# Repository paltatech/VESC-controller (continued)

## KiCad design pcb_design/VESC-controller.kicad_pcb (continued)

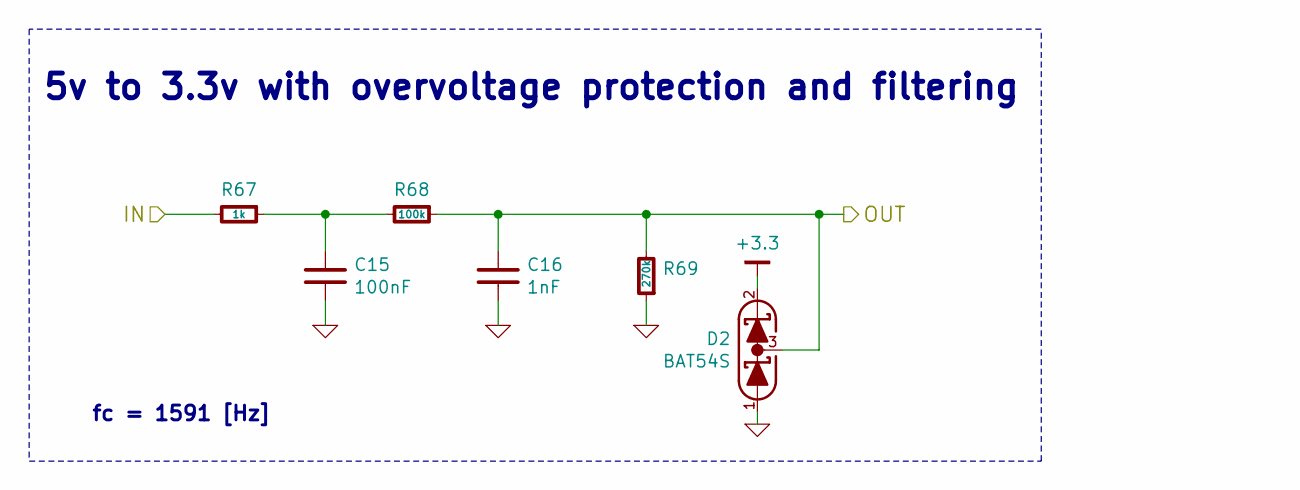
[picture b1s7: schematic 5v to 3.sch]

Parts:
C13: 100nF; CAPC1608X55; MPN GRM188R71E104KA01D
C14: 1nF; CAPC1608X55; MPN GRM188R71H102KA01D
D1: BAT54S; SOT-23; mfg# TBAT54S,LM
R64: 1k; RESC1608X50; MPN RC0603FR-071KL
R65: 100k; RESC1608X50; MPN RC0603FR-07100KL
R66: 270k; RESC1608X50; MPN RC0603FR-07270KL

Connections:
+3.3: D1.2 (K); also elsewhere on the board
/Accel input conditioning/IN: R64.2; also elsewhere on the board
/STM32F4/ADC_15: C14.1, D1.3 (COM), R65.1, R66.2; also elsewhere on the board
unnamed: C13.1, R64.1, R65.2

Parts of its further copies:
C15: 100nF; CAPC1608X55; MPN GRM188R71E104KA01D
C16: 1nF; CAPC1608X55; MPN GRM188R71H102KA01D
D2: BAT54S; SOT-23; mfg# TBAT54S,LM
R67: 1k; RESC1608X50; MPN RC0603FR-071KL
R68: 100k; RESC1608X50; MPN RC0603FR-07100KL
R69: 270k; RESC1608X50; MPN RC0603FR-07270KL

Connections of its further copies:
+3.3: D2.2 (K); also elsewhere on the board
/Regen input conditioning/IN: R67.2; also elsewhere on the board
/STM32F4/ADC_8: C16.1, D2.3 (COM), R68.1, R69.2; also elsewhere on the board
unnamed: C15.1, R67.1, R68.2

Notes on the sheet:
5v to 3.3v with overvoltage protection and filtering
fc = 1591 [Hz]

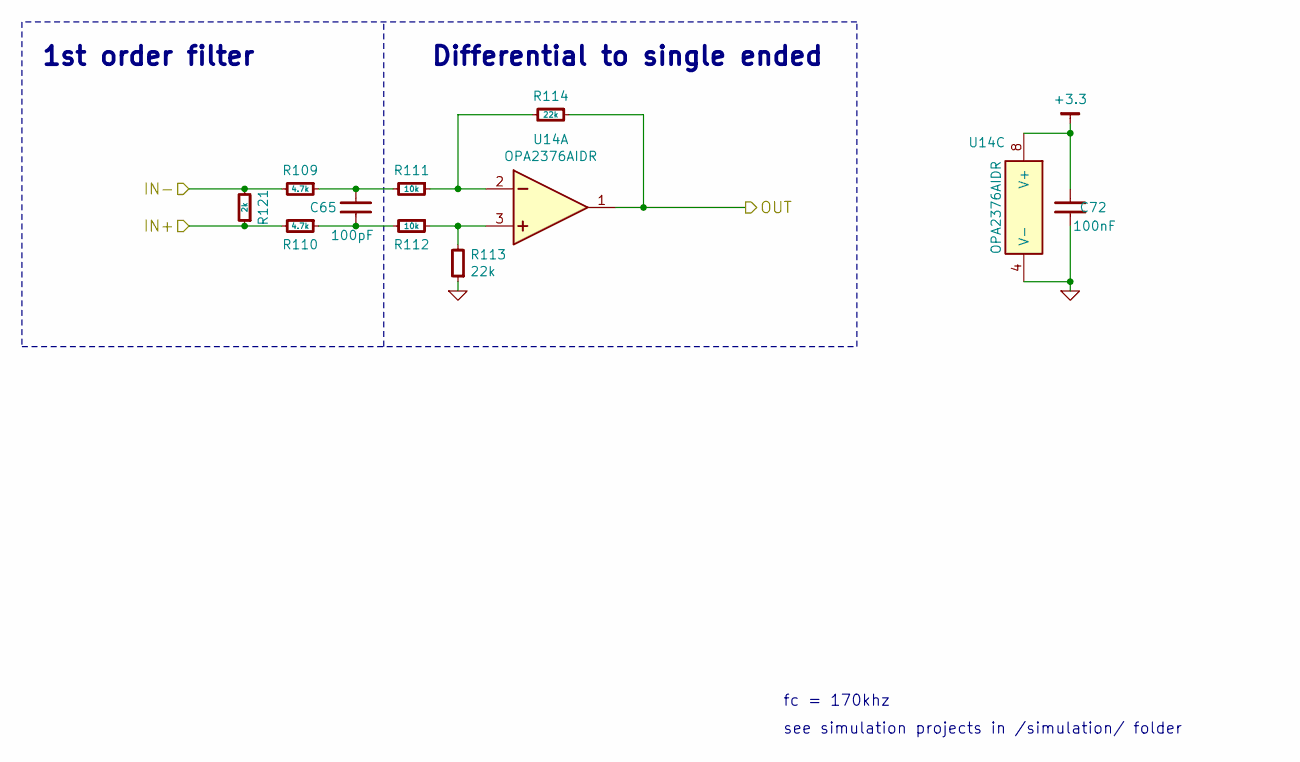
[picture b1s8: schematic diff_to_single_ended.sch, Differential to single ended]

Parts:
C65: 100pF; CAPC1608X55; MPN C0603C101J5GACTU
C72: 100nF; CAPC1608X55; MPN GRM188R71E104KA01D
R109, R110: 4.7k; RESC1608X50; MPN RC0603FR-074K7L
R111, R112: 10k; RESC1608X50; MPN RC0603FR-0710KL
R113, R114: 22k; RESC1608X50; MPN RC0603FR-0722KL
R121: 2k; RESC1608X50; MPN RC0603FR-072KL
U14: OPA2376AIDR; SOIC127P600X175-8; MPN OPA2376AIDR

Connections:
+3.3: C72.1, U14.8 (V+); also elsewhere on the board
/V_bus+: R110.2, R121.1; also elsewhere on the board
/V_bus-: R109.2, R121.2; also elsewhere on the board
/Vbus_conditioning/OUT: R114.1, U14.1 (OUT); also elsewhere on the board
unnamed: C65.1, R109.1, R111.2
unnamed: C65.2, R110.1, R112.2
unnamed: R111.1, R114.2, U14.2 (IN-)
unnamed: R112.1, R113.2, U14.3 (IN+)

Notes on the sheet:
Differential to single ended
1st order filter
fc = 170khz
see simulation projects in /simulation/ folder

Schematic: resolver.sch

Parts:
C73, C74, C75, C77, C81, C82, C85, C86, C87: 100nF; CAPC1608X55; MPN GRM188R71E104KA01D
C76, C78: 2.2uF; CAPC1608X55; MPN GRM188R71A225KE15D
C79, C80: 15pF; CAPC1608X55; MPN GCM1885C1H150JA16D
C83, C84: 120pF; CAPC1608X55; MPN C0603C121F5GACTU
C88, C89: 22uF; CAPC2012X70; mfg# C2012X5R1V226M125AC
E5, E6: BEAD-220ohm@100khz; INDC2012X130; mfg# BLM21PG221SN1D
R124, R125: 68.1k; RESC1608X50; MPN RC0603FR-0768K1L
R126, R128, R130, R131: 10k; RESC1608X50; MPN RC0603FR-0710KL
R127, R129: 22k; RESC1608X50; MPN RC0603FR-0722KL
R132, R133: 15.4k; RESC1608X50; MPN RC0603FR-0715K4L
R136, R137: 0R; RESC1608X50; MPN RC0603JR-070RL
U15: AD2S1205; QFP80P1200X1200X160-44; mfg# AD2S1205
U18: SN74LVC1G; SC-70-6; mfg# SN74LVC1G11IDCKRQ1
U19: AD8397; SOIC127P600X175-8; mfg# AD8397ARZ
U20: APX809; SOT-23; mfg# APX809-46SRG-7
U21: NCV78Mxx; TO-252; mfg# NCV78M12BDTRKG
X1: ABM3B - 8MHz; OSCCC320X500X150; mfg# ABM3B-8.000MHZ-10-1UT

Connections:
+3.3: C75.1, U18.5 (VCC); also elsewhere on the board
+12: C85.1, C88.1, C89.1, E6.2, R127.2, R129.2, U19.8 (V+)
/STM32F4/PB3: U15.4 (~SAMPLE); also elsewhere on the board
/STM32F4/PC12: U15.5 (~RDVEL); also elsewhere on the board
/STM32F4/PD2: U18.4 (QA); also elsewhere on the board
/STM32F4/SPI3_NSS: U15.2 (RD), U15.3 (~CS); also elsewhere on the board
/resolver/CLK: U15.8 (DB10/SCLK); also elsewhere on the board
/resolver/COS+: R125.1, U15.41 (Cos); also elsewhere on the board
/resolver/COS-: R125.2, U15.40 (CosLO); also elsewhere on the board
/resolver/EXC+: C83.1, R132.1, U19.7 (OUT); also elsewhere on the board
/resolver/EXC-: C84.1, R133.1, U19.1 (OUT); also elsewhere on the board
/resolver/EXC_SOURCE+: R126.2, U15.34 (EXC)
/resolver/EXC_SOURCE-: R128.2, U15.35 (~EXC)
/resolver/MISO: U15.7 (DB11/SO); also elsewhere on the board
/resolver/SIN+: R124.1, U15.37 (Sin); also elsewhere on the board
/resolver/SIN-: R124.2, U15.38 (SinLO); also elsewhere on the board
unnamed: C77.1, C78.1, E5.1, U15.39 (AVDD)
unnamed: C79.1, U15.22 (CLKIN), X1.1
unnamed: C80.1, U15.21 (XTALOUT), X1.3
unnamed: C81.1, R129.1, R131.2, U19.3 (IN+)
unnamed: C82.1, R127.1, R130.2, U19.5 (IN+)
unnamed: C83.2, R126.1, R132.2, U19.6 (IN-)
unnamed: C84.2, R128.1, R133.2, U19.2 (IN-)
unnamed: C87.1, E6.1, U21.2 (OUT)
unnamed: R136.2, U15.31 (FS1)
unnamed: R137.2, U15.32 (FS2)
unnamed: U15.6 (~SOE), U18.1 (D1A)
unnamed: U15.29 (~DOS), U18.3 (D2A)
unnamed: U15.30 (~LOT), U18.6 (D3A)
unnamed: U15.33 (~RESET), U20.2

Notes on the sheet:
Resolver interface
Buffer
This is an alternative buffer suggested here: http://www.analog.com/en/analog-dialogue/articles/precision-rtdc-measures-angular-position-and-velocity.html It seems to invert the signal... Its more expensive, but much simpler and smaller
RESET line requires a voltage monitor

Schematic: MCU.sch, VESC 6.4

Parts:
C10, C11, C12, C30, C32, C34: 100nF; CAPC1608X55; MPN GRM188R71E104KA01D
C17, C33: 15pF; CAPC1608X55; MPN GCM1885C1H150JA16D
C28, C29, C31: 2.2uF; CAPC1608X55; MPN GRM188R71A225KE15D
E4: BEAD-220ohm@100khz; INDC2012X130; MPN BLM21PG221SN1D
J9: SWD; CONN-100MIL-M-1x5
R122: 1k; RESC1608X50; MPN RC0603FR-071KL
SW1: BOOTLOADER; SMD-Switch_B3U-1000-B; mfg# B3U-1000P
U1: STM32F40X_LQFP64; QFP50P1200X1200X100-64; MPN STM32F405RGT6
X2: ABM3B - 8MHz; OSCCC320X500X150; mfg# ABM3B-8.000MHZ-10-1UT

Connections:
+3.3: C10.1, C11.1, C12.1, C34.1, E4.2, J9.1, SW1.2, U1.1 (VBAT), U1.19 (VDD), U1.32 (VDD), U1.48 (VDD), U1.64 (VDD); also elsewhere on the board
+3.3A: C30.1, C31.1, E4.1, U1.13 (VDDA); also elsewhere on the board
/Filters/HALL1_OUT: U1.37 (PC6); also elsewhere on the board
/Filters/HALL2_OUT: U1.38 (PC7); also elsewhere on the board
/Filters/HALL3_OUT: U1.39 (PC8); also elsewhere on the board
/Filters/TEMP_IN: U1.24 (PC4(ADC12_IN14)); also elsewhere on the board
/Isolated CAN/CAN_RX: U1.61 (PB8); also elsewhere on the board
/Isolated CAN/CAN_TX: U1.62 (PB9); also elsewhere on the board
/Protected GPIOs/IN1: U1.58 (PB6); also elsewhere on the board
/Protected GPIOs/IN2: U1.23 (PA7(ADC12_IN7)); also elsewhere on the board
/STM32F4/ADC_8: U1.26 (PB0(ADC12_IN8)); also elsewhere on the board
/STM32F4/ADC_15: U1.25 (PC5(ADC12_IN15)); also elsewhere on the board
/STM32F4/ADC_TEMP: U1.17 (PA3(ADC123_IN3)); also elsewhere on the board
/STM32F4/LED_GREEN: U1.28 (PB2-BOOT1); also elsewhere on the board
/STM32F4/LED_RED: U1.27 (PB1(ADC12_IN9)); also elsewhere on the board
/STM32F4/NRST: C32.1, J9.5, U1.7 (NRST)
/STM32F4/PB3: U1.55 (PB3(JTDO/TRACESWO)); also elsewhere on the board
/STM32F4/PB4: U1.56 (PB4(NJTRST)); also elsewhere on the board
/STM32F4/PC9: U1.40 (PC9); also elsewhere on the board
/STM32F4/PC12: U1.53 (PC12); also elsewhere on the board
/STM32F4/PD2: U1.54 (PD2); also elsewhere on the board
/STM32F4/PWM_UB: U1.34 (PB13(OTG_HS_VBUS)); also elsewhere on the board
/STM32F4/PWM_UT: U1.41 (PA8); also elsewhere on the board
/STM32F4/PWM_VB: U1.35 (PB14); also elsewhere on the board
/STM32F4/PWM_VT: U1.42 (PA9(OTG_FS_VBUS)); also elsewhere on the board
/STM32F4/PWM_WB: U1.36 (PB15); also elsewhere on the board
/STM32F4/PWM_WT: U1.43 (PA10); also elsewhere on the board
/STM32F4/RX_SDA_NSS: U1.30 (PB11); also elsewhere on the board
/STM32F4/SPI3_NSS: U1.50 (PA15(JTDI)); also elsewhere on the board
/STM32F4/SWCLK: J9.2, U1.49 (PA14(JTCK-SWCLK))
/STM32F4/SWDIO: J9.4, U1.46 (PA13(JTMS-SWDIO))
/STM32F4/TX_SCL_MOSI: U1.29 (PB10); also elsewhere on the board
/STM32F4/USB_D+: U1.45 (PA12); also elsewhere on the board
/STM32F4/USB_D-: U1.44 (PA11); also elsewhere on the board
/STM32F4/~DRIVER_RESET: U1.3 (PC14-OSC32_IN); also elsewhere on the board
/STM32F4/~FAULT: U1.33 (PB12); also elsewhere on the board
/Supervisor/CLR_OC_Fault: U1.57 (PB5); also elsewhere on the board
/Supervisor/OC_Fault: U1.59 (PB7); also elsewhere on the board
/Vbus_conditioning/OUT: U1.11 (PC3(ADC123_IN13)); also elsewhere on the board
/conditioning U/I_phase: U1.8 (PC0(ADC123_IN10)); also elsewhere on the board
/conditioning U/TEMP: U1.20 (PA4(ADC12_IN4/DAC1_OUT)); also elsewhere on the board
/conditioning U/V_phase: U1.14 (PA0(ADC123_IN0/WKUP)); also elsewhere on the board
/conditioning V/I_phase: U1.9 (PC1(ADC123_IN11)); also elsewhere on the board
/conditioning V/TEMP: U1.21 (PA5(ADC12_IN5/DAC2_OUT)); also elsewhere on the board
/conditioning V/V_phase: U1.15 (PA1(ADC123_IN1)); also elsewhere on the board
/conditioning W/I_phase: U1.10 (PC2(ADC123_IN12)); also elsewhere on the board
/conditioning W/TEMP: U1.22 (PA6(ADC12_IN6)); also elsewhere on the board
/conditioning W/V_phase: U1.16 (PA2(ADC123_IN2)); also elsewhere on the board
/resolver/CLK: U1.51 (PC10); also elsewhere on the board
/resolver/MISO: U1.52 (PC11); also elsewhere on the board
unnamed: C17.2, U1.5 (PH0-OSC_IN), X2.1
unnamed: C28.2, U1.31 (VCAP1)
unnamed: C29.2, U1.47 (VCAP2)
unnamed: C33.2, U1.6 (PH1-OSC_OUT), X2.3
unnamed: R122.1, SW1.1, U1.60 (BOOT0(VPP))

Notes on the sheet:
Bypass, place next to VDD pins
vesc vanilla uses PB7!
remember it should be pulled down if you want to enter bootloader
PIN ---------------------------------- FAULT SPI_CS LED_GREEN ACCEL REGEN GATE DRIVER RST
| VESC Vanilla | PB7 | PC9 (drv) | PB0 | - | - | -
| VESC-controller | PB12 (could enable BRK) | PA15 (resolver) | PB2 | PC5 (AN15) | PB0 (AN8) | PC14
Changes for board support package
STM32F405 MCU

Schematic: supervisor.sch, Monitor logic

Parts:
C18, C19, C20, C21: 100nF; CAPC1608X55; MPN GRM188R71E104KA01D
C93: 220pF; CAPC1608X55; MPN GRM1885C1H221JA01D
D19: BAT54S; SOT-23; mfg# TBAT54S,LM
DS3: OCP; LED-0603; MPN LTST-C191KRKT
DS6: FAULT; LED-0603; MPN LTST-C191KRKT
R26, R27, R28, R29, R30, R31, R32, R33: 4.7k; RESC1608X50; MPN RC0603FR-074K7L
R86, R141: 100R; RESC1608X50; MPN RC0603FR-07100RL
R123: 22R; RESC1608X50; MPN RC0603FR-0722RL
R138: 10k; RESC1608X50; MPN RC0603FR-0710KL
U5: 7400-TSSOP; SOP65P640X110-14; MPN SN74LVC00APWR
U6: SN74ACT08PWR; SOP65P640X110-14; mfg# SN74ACT08PWR
U7: SN74ACT08PWR; SOP65P640X110-14; MPN SN74ACT08PWR
U8: SN74AUP1G74; SOP50P310X100-8; MPN SN74AUP1G74DCUR

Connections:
+3.3: C18.2, C21.2, D19.2 (K), DS6.2 (A), R26.1, R33.1, R86.1, R138.2, U5.14 (V+), U8.2 (D), U8.7 (~PRE), U8.8 (VCC); also elsewhere on the board
/STM32F4/PWM_UB: R30.1, U5.2 (D2A), U6.5 (D2B); also elsewhere on the board
/STM32F4/PWM_UT: R27.1, U5.1 (D1A), U6.1 (D1A); also elsewhere on the board
/STM32F4/PWM_VB: R31.1, U5.5 (D2B), U6.13 (D2D); also elsewhere on the board
/STM32F4/PWM_VT: R28.1, U5.4 (D1B), U6.9 (D1C); also elsewhere on the board
/STM32F4/PWM_WB: R32.1, U5.10 (D2C), U7.5 (D2B); also elsewhere on the board
/STM32F4/PWM_WT: R29.1, U5.9 (D1C), U7.1 (D1A); also elsewhere on the board
/STM32F4/~DRIVER_RESET: U7.9 (D1C); also elsewhere on the board
/STM32F4/~FAULT: C93.1, D19.3 (COM), R123.1, R141.2, U7.10 (D2C); also elsewhere on the board
/Supervisor/CLR_OC_Fault: U8.6 (~CLR); also elsewhere on the board
/Supervisor/OC_Fault: U8.5 (Q); also elsewhere on the board
/Supervisor/PWM_GUT: U6.3 (QA); also elsewhere on the board
/Supervisor/PWM_GVT: U6.8 (QC); also elsewhere on the board
/Supervisor/PWM_GWT: U7.3 (QA); also elsewhere on the board
/conditioning U/PWM_B: U6.6 (QB); also elsewhere on the board
/conditioning U/~OC_Fault: R26.2, U5.13 (D2D); also elsewhere on the board
/conditioning V/PWM_B: U6.11 (QD); also elsewhere on the board
/conditioning W/PWM_B: U7.6 (QB); also elsewhere on the board
unnamed: DS3.1 (K), U7.13 (D2D), U8.3 (~Q)
unnamed: DS3.2 (A), R86.2
unnamed: DS6.1 (K), R141.1
unnamed: R33.2, U5.12 (D1D)
unnamed: U5.3 (QA), U6.2 (D2A), U6.4 (D1B)
unnamed: U5.6 (QB), U6.10 (D2C), U6.12 (D1D)
unnamed: U5.8 (QC), U7.2 (D2A), U7.4 (D1B)
unnamed: U5.11 (QD), U8.1 (CLK)
unnamed: U7.8 (QC), U7.12 (D1D)
~DRIVER_RESET: U7.11 (QD); also elsewhere on the board
~FAULT: R123.2, R138.1; also elsewhere on the board

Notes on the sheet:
PWM overlap elimination
AND: 2.9ns propagation delay
Overcurrent latch
If FAULT, or OCP, or RESET is triggered, RESET driver
pulldowns to assert MCU pins in high-Z state during boot

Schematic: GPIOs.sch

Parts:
DZ4, DZ5: MMSZ52XXB; SOD-123
Q4, Q5: SI2302; SOT-23; MPN SI2302
R152, R153: 1k; RESC1608X50; MPN RC0603FR-071KL
R154, R155, R156, R157: NI; RESC1608X50; MPN RC0603FR-071KL

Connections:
/Protected GPIOs/IN1: Q4.1 (G), R152.2, R154.1; also elsewhere on the board
/Protected GPIOs/IN2: Q5.1 (G), R153.2, R155.1; also elsewhere on the board
/Protected GPIOs/OUT1: DZ4.1 (K), Q4.3 (D), R154.2, R156.1; also elsewhere on the board
/Protected GPIOs/OUT2: DZ5.1 (K), Q5.3 (D), R155.2, R157.1; also elsewhere on the board

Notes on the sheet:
Protected, 1A Open drain outputs

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
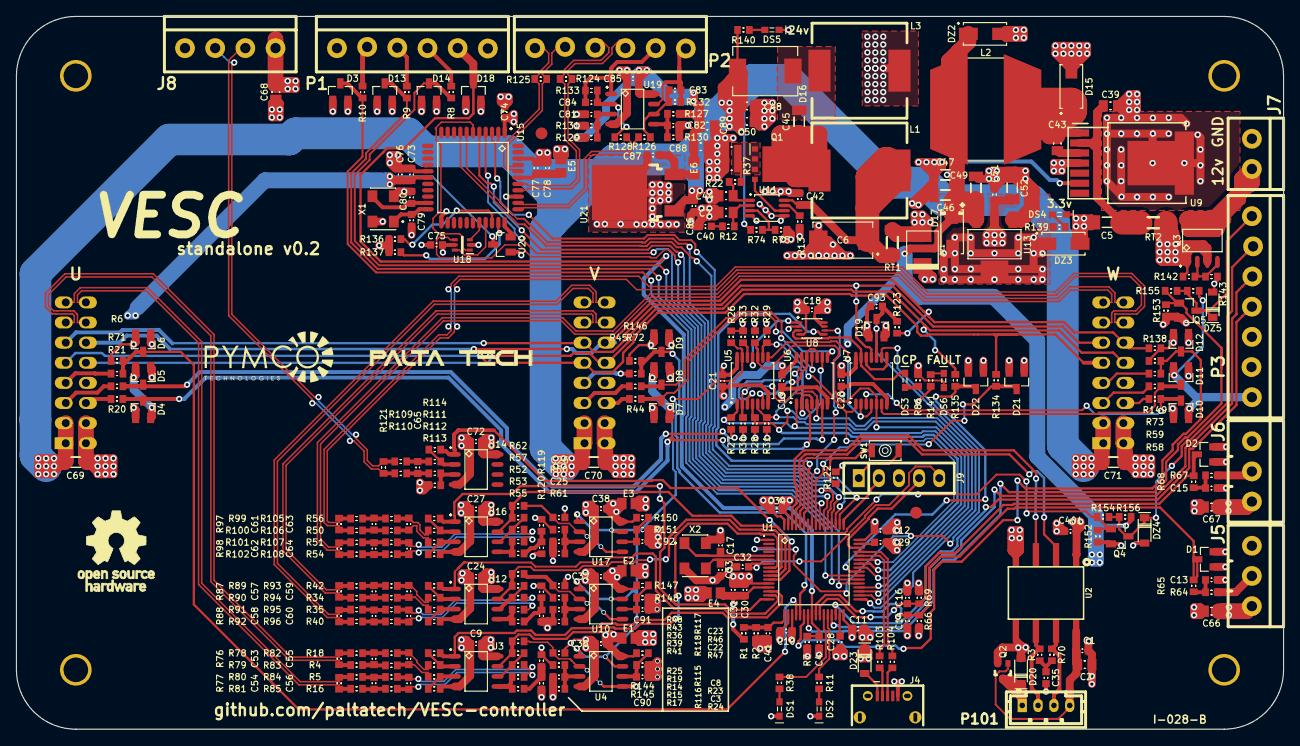
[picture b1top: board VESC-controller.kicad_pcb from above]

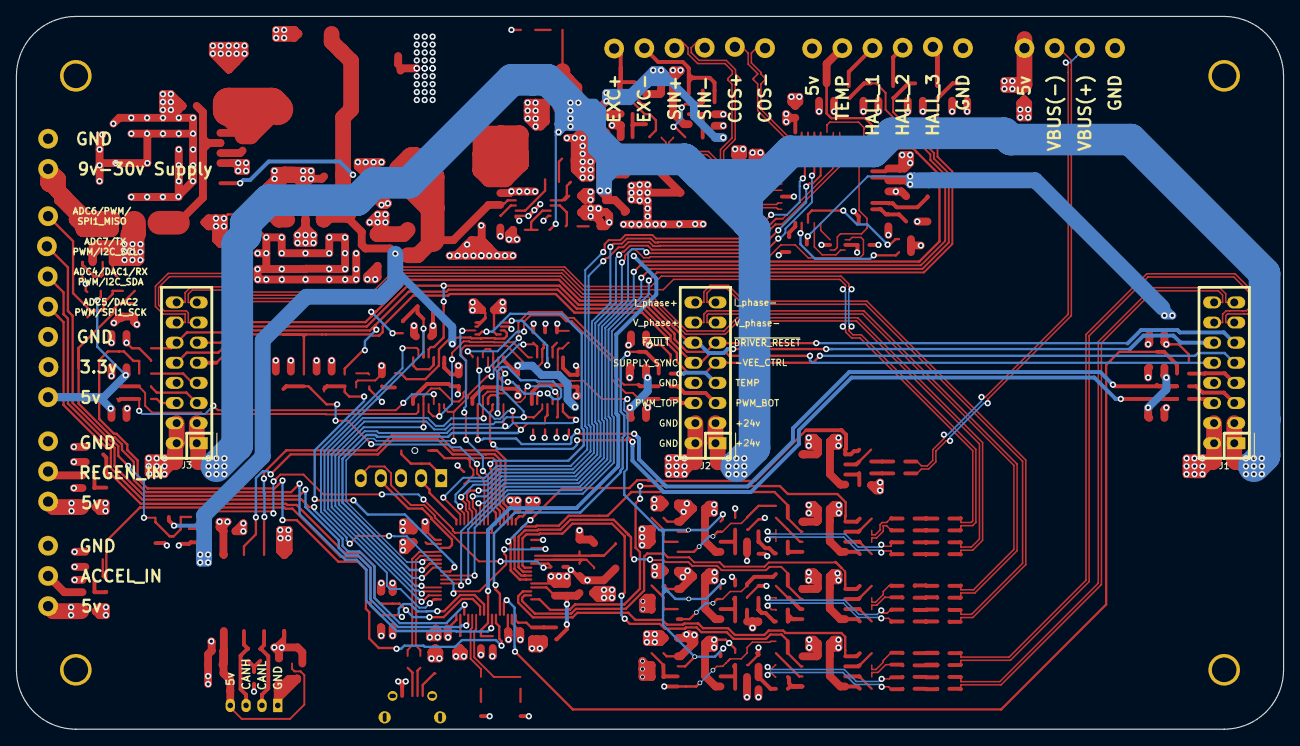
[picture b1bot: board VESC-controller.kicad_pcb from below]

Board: 4 copper layers, 160.0 x 90.0 mm, 336 parts (3 on the bottom side), 217 nets.

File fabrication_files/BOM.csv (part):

Refs,Value,Footprint,QTY,MFR,MPN,SPR,SPN
RT1,FUSE 5A SLOW,IPC7351-Most:RESC3216X60,1,Bel Fuse Inc.,C1S 5,Digikey,507-1194-1-ND
RT2,POLYFUSE 1A,IPC7351-Most:RESC3216X60,1,Bel Fuse Inc.,0ZCJ0050AF2E,Digikey,507-1803-1-ND
C401;C1;C35;C18;C21;C20;C19;C74;C73;C77;C82;C81;C85;C75;C87;C86;C51;C13;C13;C32;C30;C34;C10;C11;C12;C3;C9;C36;C3;C9;C36;C3;C9;C36;C72,100nF,IPC7351-Nominal:CAPC1608X55,35,Murata Electronics North America,GRM188R71E104KA01D,Digikey,490-1524-1-ND
C8;C8;C8;C65,100pF,IPC7351-Nominal:CAPC1608X55,4,KEMET,C0603C101J5GACTU,Digikey,399-1061-1-ND
C83;C84,120pF,IPC7351-Nominal:CAPC1608X55,2,KEMET,C0603C121F5GACTU,Digikey,399-7850-1-ND
C79;C80;C17;C33,15pF,IPC7351-Nominal:CAPC1608X55,4,Murata Electronics North America,GCM1885C1H150JA16D,Digikey,490-4957-1-ND
C40;C42,180nF,IPC7351-Nominal:CAPC1608X55,2,Murata Electronics North America,GRM188R71E184KA88D,Digikey,490-6431-1-ND
C14;C14,1nF,IPC7351-Nominal:CAPC1608X55,2,Murata Electronics North America,GRM188R71H102KA01D,Digikey,490-1494-1-ND
C53;C54;C53;C54;C53;C54,2.2nF,IPC7351-Nominal:CAPC1608X55,6,Murata Electronics North America,GRM188R71H222KA01D,Digikey,490-1500-1-ND
C76;C78;C41;C31;C28;C29;C4,2.2uF,IPC7351-Nominal:CAPC1608X55,7,Murata Electronics North America,GRM188R71A225KE15D,Digikey,490-4520-1-ND
C55;C56;C55;C56;C55;C56,220pF,IPC7351-Nominal:CAPC1608X55,6,Murata Electronics North America,GRM1885C1H221JA01D,Digikey,490-1435-1-ND
R37,18mOhm,IPC7351-Nominal:CAPC1632X76,1,Susumu,PRL1632-R018-F-T1,Digikey,PRL1632.018FCT-ND
C39;C43,1uF 50v,IPC7351-Nominal:CAPC2012X70,2,Taiyo Yuden,UMK212B7105KG-T,Digikey,UMK212B7105KG-T
C88;C89;C48;C50,22uF,IPC7351-Nominal:CAPC2012X70,4,TDK Corporation,C2012X5R1V226M125AC,Digikey,445-14428-1-ND
C2;C68;C66;C67,4.7uF,IPC7351-Nominal:CAPC2012X70,4,Murata Electronics North America,GRM21BR71A475KA73K,Digikey,490-6479-1-ND
C44,680pF,IPC7351-Nominal:CAPC2012X70,1,"Samsung Electro-Mechanics America, Inc.",CL21C751JBCNNNC,Digikey,1276-2691-1-ND
C7,750pF,IPC7351-Nominal:CAPC2012X70,1,"Samsung Electro-Mechanics America, Inc.",CL21C751JBCNNNC,Digikey,1276-2691-1-ND
C5,10uF 35v,IPC7351-Nominal:CAPC3216X70,1,Taiyo Yuden,GMK316AB7106KL-TR,Digikey,587-3007-1-ND
C45,2.2uF 50v,IPC7351-Nominal:CAPC3216X70,1,Murata Electronics North America,GRM31CR71H225KA88L,Digikey,490-3367-1-ND
C46;C47;C49;C52,22uF 10v,IPC7351-Nominal:CAPC3216X70,4,Taiyo Yuden,LMK316AB7226ML-TR,Digikey,587-2782-1-ND
C71;C70;C69,4.7uF 50v,IPC7351-Nominal:CAPC3216X70,3,Murata Electronics North America,GRM31CR71H475KA12L,Digikey,490-6521-1-ND
C6,4.7uF 50v tant,IPC7351-Nominal:CAPMP7343X310,1,Vishay Sprague,593D475X9050D2TE3,Digikey,718-1107-1-ND
D15;D17,SS16,IPC7351-Nominal:DIOM5326X292,2,Fairchild/ON Semiconductor,SS16,Digikey,SS16FSCT-ND
D16,30BQ100TR,IPC7351-Nominal:DIOM7959X265,1,SMC Diode Solutions,30BQ100TR,Digikey,1655-1389-1-ND
E5;E6;E4;E1;E1;E1,BEAD-220ohm@100khz,IPC7351-Nominal:INDC2012X130,6,Murata Electronics North America,BLM21PG221SN1D,Digikey,490-1054-1-ND
L1;L3,22uH 5.2A,IPC7351-Nominal:INDC3225X135,2,Bourns Inc.,SRR1210-220M,Digikey,SRR1210-220MCT-ND
X1;X2,ABM3B - 8MHz,IPC7351-Nominal:OSCCC320X500X150,2,Abracon LLC,ABM3B-8.000MHZ-10-1UT,Digikey,535-9721-1-ND
U1,STM32F40X_LQFP64,IPC7351-Nominal:QFP50P1200X1200X100-64,1,STMicroelectronics,STM32F405RGT6,Digikey,497-11767-ND
U15,AD2S1205,IPC7351-Nominal:QFP80P1200X1200X160-44,1,Analog Devices Inc.,AD2S1205YSTZ,Digikey,AD2S1205YSTZ-ND
R136;R137;R6,0R,IPC7351-Nominal:RESC1608X50,3,Yageo,RC0603JR-070RL,Digikey,311-0.0GRCT-ND
R12,1.78k,IPC7351-Nominal:RESC1608X50,1,Yageo,RC0603FR-071K78L,Digikey,311-1.78KHRCT-ND
R86;R141;R22;R78;R79;R80;R81;R78;R79;R80;R81;R38;R11;R135;R134;R78;R79;R80;R81,100R,IPC7351-Nominal:RESC1608X50,19,Yageo,RC0603FR-07100RL,Digikey,311-100HRCT-ND
R65;R65,100k,IPC7351-Nominal:RESC1608X50,2,Yageo,RC0603FR-07100KL,Digikey,311-100KHRCT-ND
R138;R126;R130;R128;R131;R75;R143;R142;R2;R10;R9;R8;R7;R18;R16;R19;R17;R25;R24;R18;R16;R19;R17;R25;R24;R140;R18;R16;R19;R17;R25;R24;R111;R112;R114;R113,10k,IPC7351-Nominal:RESC1608X50,36,Yageo,RC0603FR-0710KL,Digikey,311-10.0KHRCT-ND
R132;R133,15.4k,IPC7351-Nominal:RESC1608X50,2,Yageo,RC0603FR-0715K4L,Digikey,311-15.4KHRCT-ND
R74,180k,IPC7351-Nominal:RESC1608X50,1,Yageo,RC0603FR-07180KL,Digikey,311-180KHRCT-ND
R64;R64;R122;R23;R82;R83;R84;R85;R116;R115;R23;R82;R83;R84;R85;R116;R115;R139;R23;R82;R83;R84;R85;R116;R115,1k,IPC7351-Nominal:RESC1608X50,25,Yageo,RC0603FR-071KL,Digikey,311-1.00KHRCT-ND
R123;R20;R21;R71;R20;R21;R71;R103;R104;R20;R21;R71,22R,IPC7351-Nominal:RESC1608X50,12,Yageo,RC0603FR-0722RL,Digikey,311-22.0HRCT-ND
R127;R129,22k,IPC7351-Nominal:RESC1608X50,2,Yageo,RC0603FR-0722KL,Digikey,311-22.0KHRCT-ND
R66;R66,270k,IPC7351-Nominal:RESC1608X50,2,Yageo,RC0603FR-07270KL,Digikey,311-270KHRCT-ND
R76;R77;R76;R77;R76;R77;R121,2k,IPC7351-Nominal:RESC1608X50,7,Yageo,RC0603FR-072KL,Digikey,311-2.00KHRCT-ND
R13,33.2k,IPC7351-Nominal:RESC1608X50,1,Yageo,RC0603FR-0733K2L,Digikey,311-33.2KHRCT-ND
R30;R27;R31;R28;R32;R29;R33;R26;R26;R26;R109;R110,4.7k,IPC7351-Nominal:RESC1608X50,12,Yageo,RC0603FR-074K7L,Digikey,311-4.70KHRCT-ND
R3;R70,60.4R,IPC7351-Nominal:RESC1608X50,2,Yageo,RC0603FR-0760R4L,Digikey,311-60.4HRCT-ND
R124;R125,68.1k,IPC7351-Nominal:RESC1608X50,2,Yageo,RC0603FR-0768K1L,Digikey,311-68.1KHRCT-ND
R4;R5;R14;R15;R4;R5;R14;R15;R4;R5;R14;R15,8.87k,IPC7351-Nominal:RESC1608X50,12,Yageo,RC0603FR-078K87L,Digikey,311-8.87KHRCT-ND
R1,NTC 10k,IPC7351-Nominal:RESC1608X50,1,Murata Electronics North America,NCP18XH103F03RB,Digikey,490-4800-1-ND
U19,AD8397,IPC7351-Nominal:SOIC127P600X175-8,1,Analog Devices Inc.,AD8397ARZ,Digikey,AD8397ARZ-ND
Q3,AO4805,IPC7351-Nominal:SOIC127P600X175-8,1,Alpha & Omega Semiconductor Inc.,AO4805,Digikey,785-1055-1-ND
U4;U4;U4,LM2903DT,IPC7351-Nominal:SOIC127P600X175-8,3,STMicroelectronics,LM2903DT,Digikey,497-1559-1-ND
U3;U3;U3;U14,OPA2376AIDR,IPC7351-Nominal:SOIC127P600X175-8,4,Texas Instruments,OPA2376AIDR,Digikey,296-22564-1-ND
U8,SN74AUP1G74,IPC7351-Nominal:SOP50P310X100-8,1,Texas Instruments,SN74AUP1G74DCUR,Digikey,296-19761-1-ND
U11,LM3488,IPC7351-Nominal:SOP65P490X109-8,1,Texas Instruments,LM3488MM/NOPB,Digikey,LM3488MM/NOPBCT-ND
U5,7400-TSSOP,IPC7351-Nominal:SOP65P640X110-14,1,Texas Instruments,SN74LVC00APWR,Digikey,296-1216-1-ND
U6;U7,SN74ACT08PWR,IPC7351-Nominal:SOP65P640X110-14,2,Texas Instruments,SN74ACT08PWR,Digikey,296-4355-1-ND
J9,SWD,conn-100mil:CONN-100MIL-M-1x5,1,,,,
J1,GATE_DRIVER_CONN_U,conn-100mil:CONN-100MIL-M-2x8,1,Amphenol FCI,67997-216HLF,Digikey,609-3238-ND
J2,GATE_DRIVER_CONN_V,conn-100mil:CONN-100MIL-M-2x8,1,Amphenol FCI,67997-216HLF,Digikey,609-3238-ND
J3,GATE_DRIVER_CONN_W,conn-100mil:CONN-100MIL-M-2x8,1,Amphenol FCI,67997-216HLF,Digikey,609-3238-ND
J4,micro USB,conn-fci:CONN-10118194-0001LF-FCI,1,Amphenol FCI,10118194-0001LF,Digikey,609-4618-1-ND
J7,12V,"conn-phoenix:mcv_1,5-2-G-3,81",1,Phoenix Contact,1803426,Digikey,277-1221-ND
J5,ACCEL,"conn-phoenix:mcv_1,5-3-G-3,81",1,Phoenix Contact,1803439,Digikey,277-1222-ND
J6,REGEN,"conn-phoenix:mcv_1,5-3-G-3,81",1,Phoenix Contact,1803439,Digikey,277-1222-ND
J8,V_BUS,"conn-phoenix:mcv_1,5-4-G-3,81",1,Phoenix Contact,1803442,Digikey,277-1223-ND
P1,HALL/Encoder,"conn-phoenix:mcv_1,5-6-G-3,81",1,Phoenix Contact,1803468,Digikey,277-1225-ND
P2,Resolver,"conn-phoenix:mcv_1,5-6-G-3,81",1,Phoenix Contact,1803468,Digikey,277-1225-ND
P3,PWR_COMM,"conn-phoenix:mcv_1,5-7-G-3,81",1,Phoenix Contact,1803471,Digikey,277-1226-ND
L2,27uH,manuf:BOURNS-SDR1307,1,Bourns Inc.,SDR1307-270ML,Digikey,SDR1307-270MLCT-ND
Q1,BSC340N08,manuf:TEXAS-Q5A,1,Infineon Technologies,BSC340N08NS3GATMA1,Digikey,BSC340N08NS3GATMA1CT-ND
U9,LM22676QTJ-5.0,manuf:TO-263-7-TEXAS,1,Texas Instruments,LM22676QTJE-5.0/NOPB,Digikey,LM22676QTJE-5.0/NOPBCT-ND
SW1,BOOTLOADER,paltatech:SMD-Switch_B3U-1000-B,1,Omron Electronics Inc-EMC Div,B3U-1000P,Digikey,SW1020CT-ND
U2,ISO1050,paltatech:SO8-ISO1050,1,Texas Instruments,ISO1050DUBR,Digikey,296-24818-1-ND
DS6,FAULT,smd-semi:LED-0603,1,Lite-On Inc.,LTST-C191KRKT,Digikey,160-1447-1-ND
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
